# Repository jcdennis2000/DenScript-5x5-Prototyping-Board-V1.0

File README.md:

# DenScript-5x5-Prototyping-Board-V1.0

This prototyping board allows you to make your own circuit and easily attach it to any project. It is 5×5 DenBlock units in size (each unit is 12mm). There are also four rails that you can use for +V, GND or any signal you wish!

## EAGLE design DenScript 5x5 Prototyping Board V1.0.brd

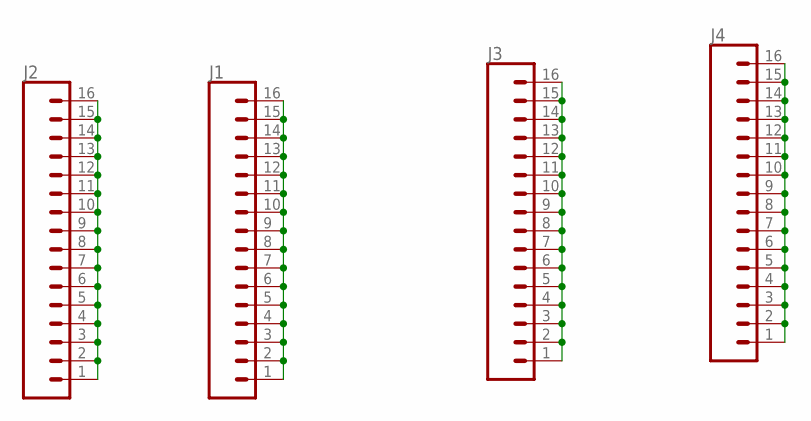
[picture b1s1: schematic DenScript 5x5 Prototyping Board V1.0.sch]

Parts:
J1, J2, J3, J4: CONN_16; 1X16

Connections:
unnamed: J2.1, J2.2, J2.3, J2.4, J2.5, J2.6, J2.7, J2.8, J2.9, J2.10, J2.11, J2.12, J2.13, J2.14, J2.15, J2.16
unnamed: J3.1, J3.2, J3.3, J3.4, J3.5, J3.6, J3.7, J3.8, J3.9, J3.10, J3.11, J3.12, J3.13, J3.14, J3.15, J3.16
unnamed: J1.1, J1.2, J1.3, J1.4, J1.5, J1.6, J1.7, J1.8, J1.9, J1.10, J1.11, J1.12, J1.13, J1.14, J1.15, J1.16
unnamed: J4.1, J4.2, J4.3, J4.4, J4.5, J4.6, J4.7, J4.8, J4.9, J4.10, J4.11, J4.12, J4.13, J4.14, J4.15, J4.16

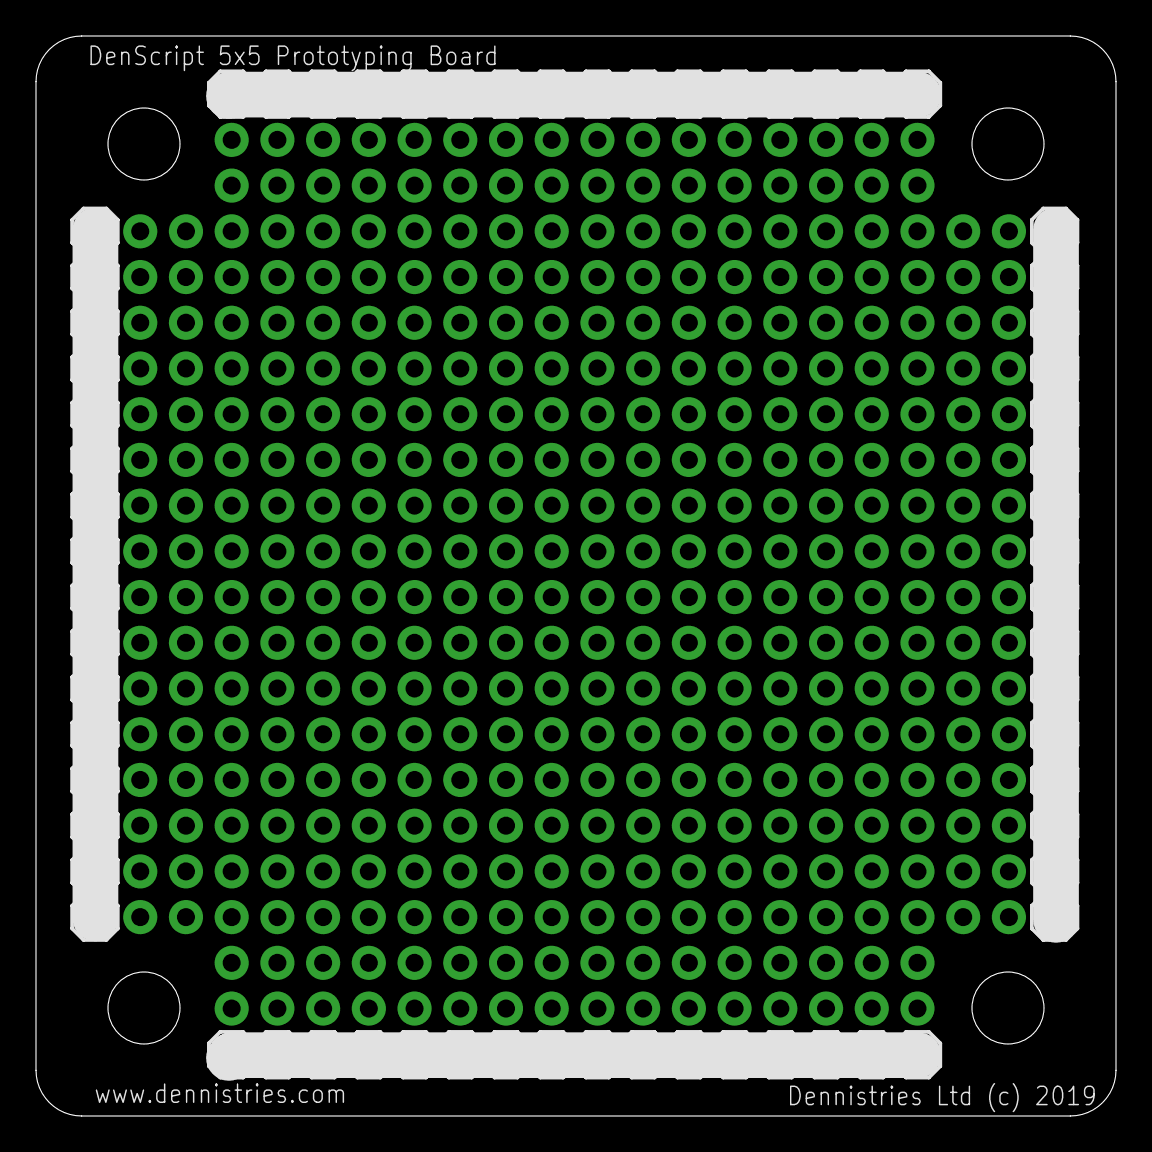
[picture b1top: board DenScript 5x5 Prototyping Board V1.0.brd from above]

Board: 2 copper layers, 60.0 x 60.0 mm, 4 parts (0 on the bottom side), 4 nets.

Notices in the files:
DenScript 5x5 Prototyping Board V1.0.brd:
Dennistries Ltd (c) 2019
parts and their libraries:
SparkFun-Connectors: Licensing: Creative Commons ShareAlike 4.0 International - https://creativecommons.org/licenses/by-sa/4.0
